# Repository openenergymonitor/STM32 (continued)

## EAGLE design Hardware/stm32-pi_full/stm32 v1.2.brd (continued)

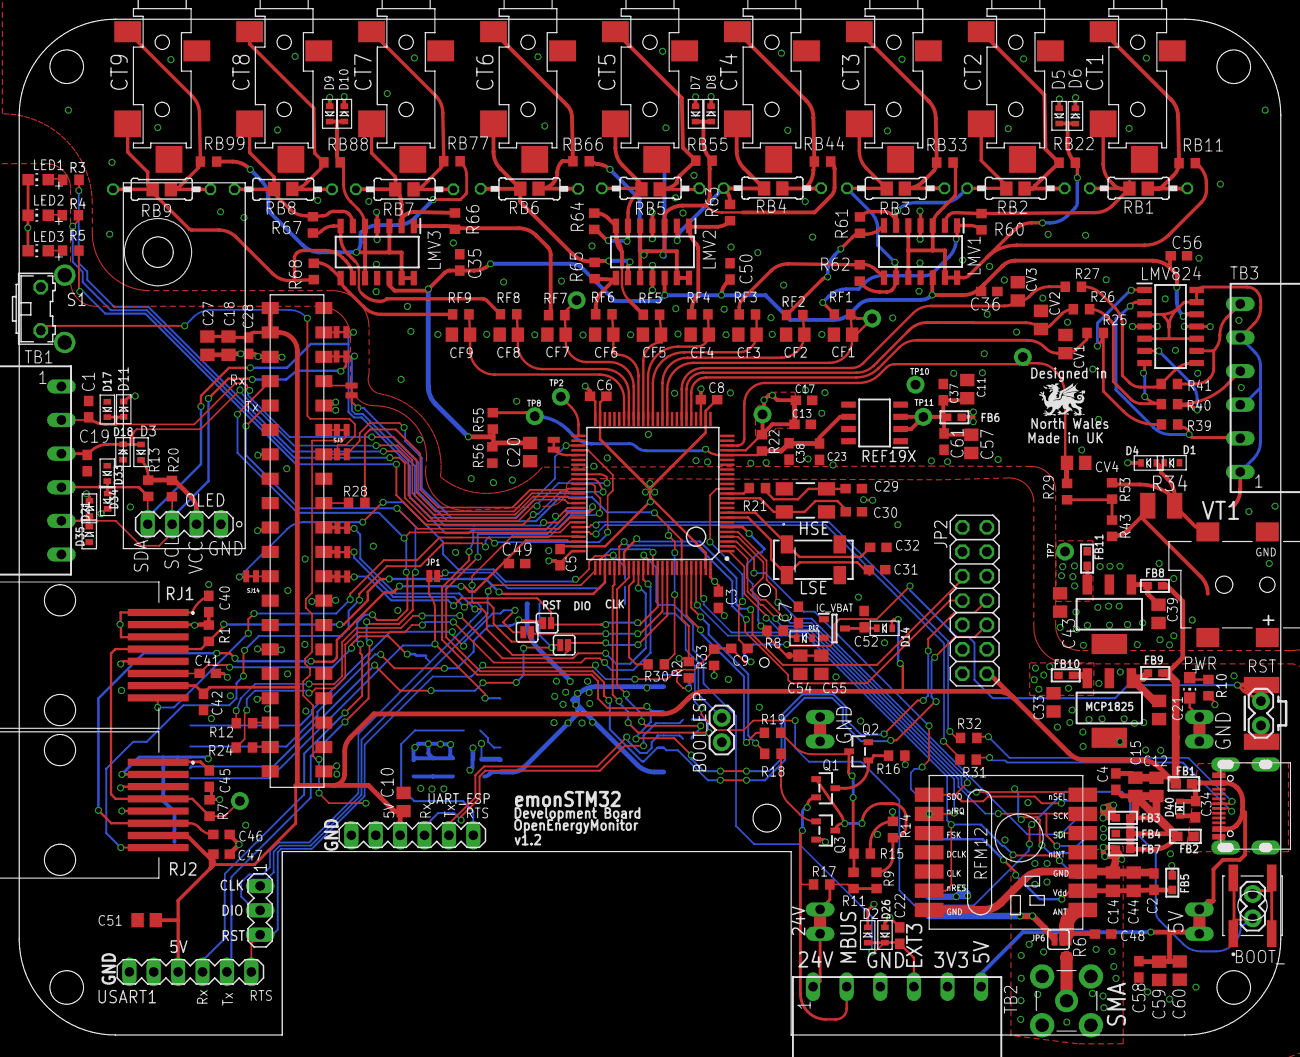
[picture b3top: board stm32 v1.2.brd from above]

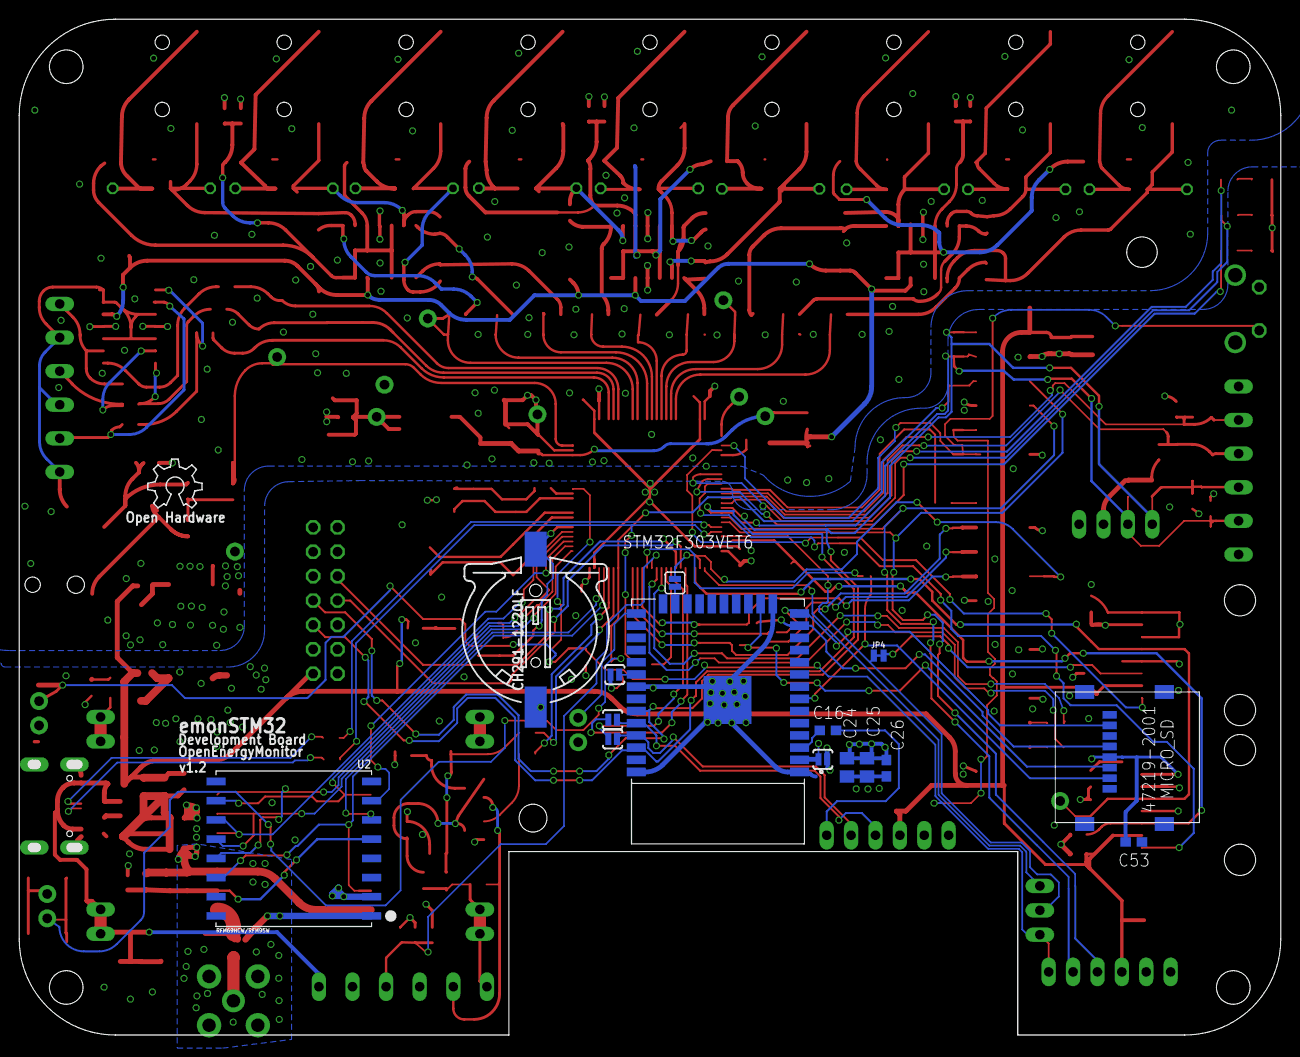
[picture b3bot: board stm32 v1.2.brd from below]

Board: 4 copper layers, 131.4 x 105.8 mm, 277 parts (16 on the bottom side), 164 nets.

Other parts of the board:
LOGO1: OSHW_LOGO_6MILX0200-NT; OSHW_6X200_NOTEXT

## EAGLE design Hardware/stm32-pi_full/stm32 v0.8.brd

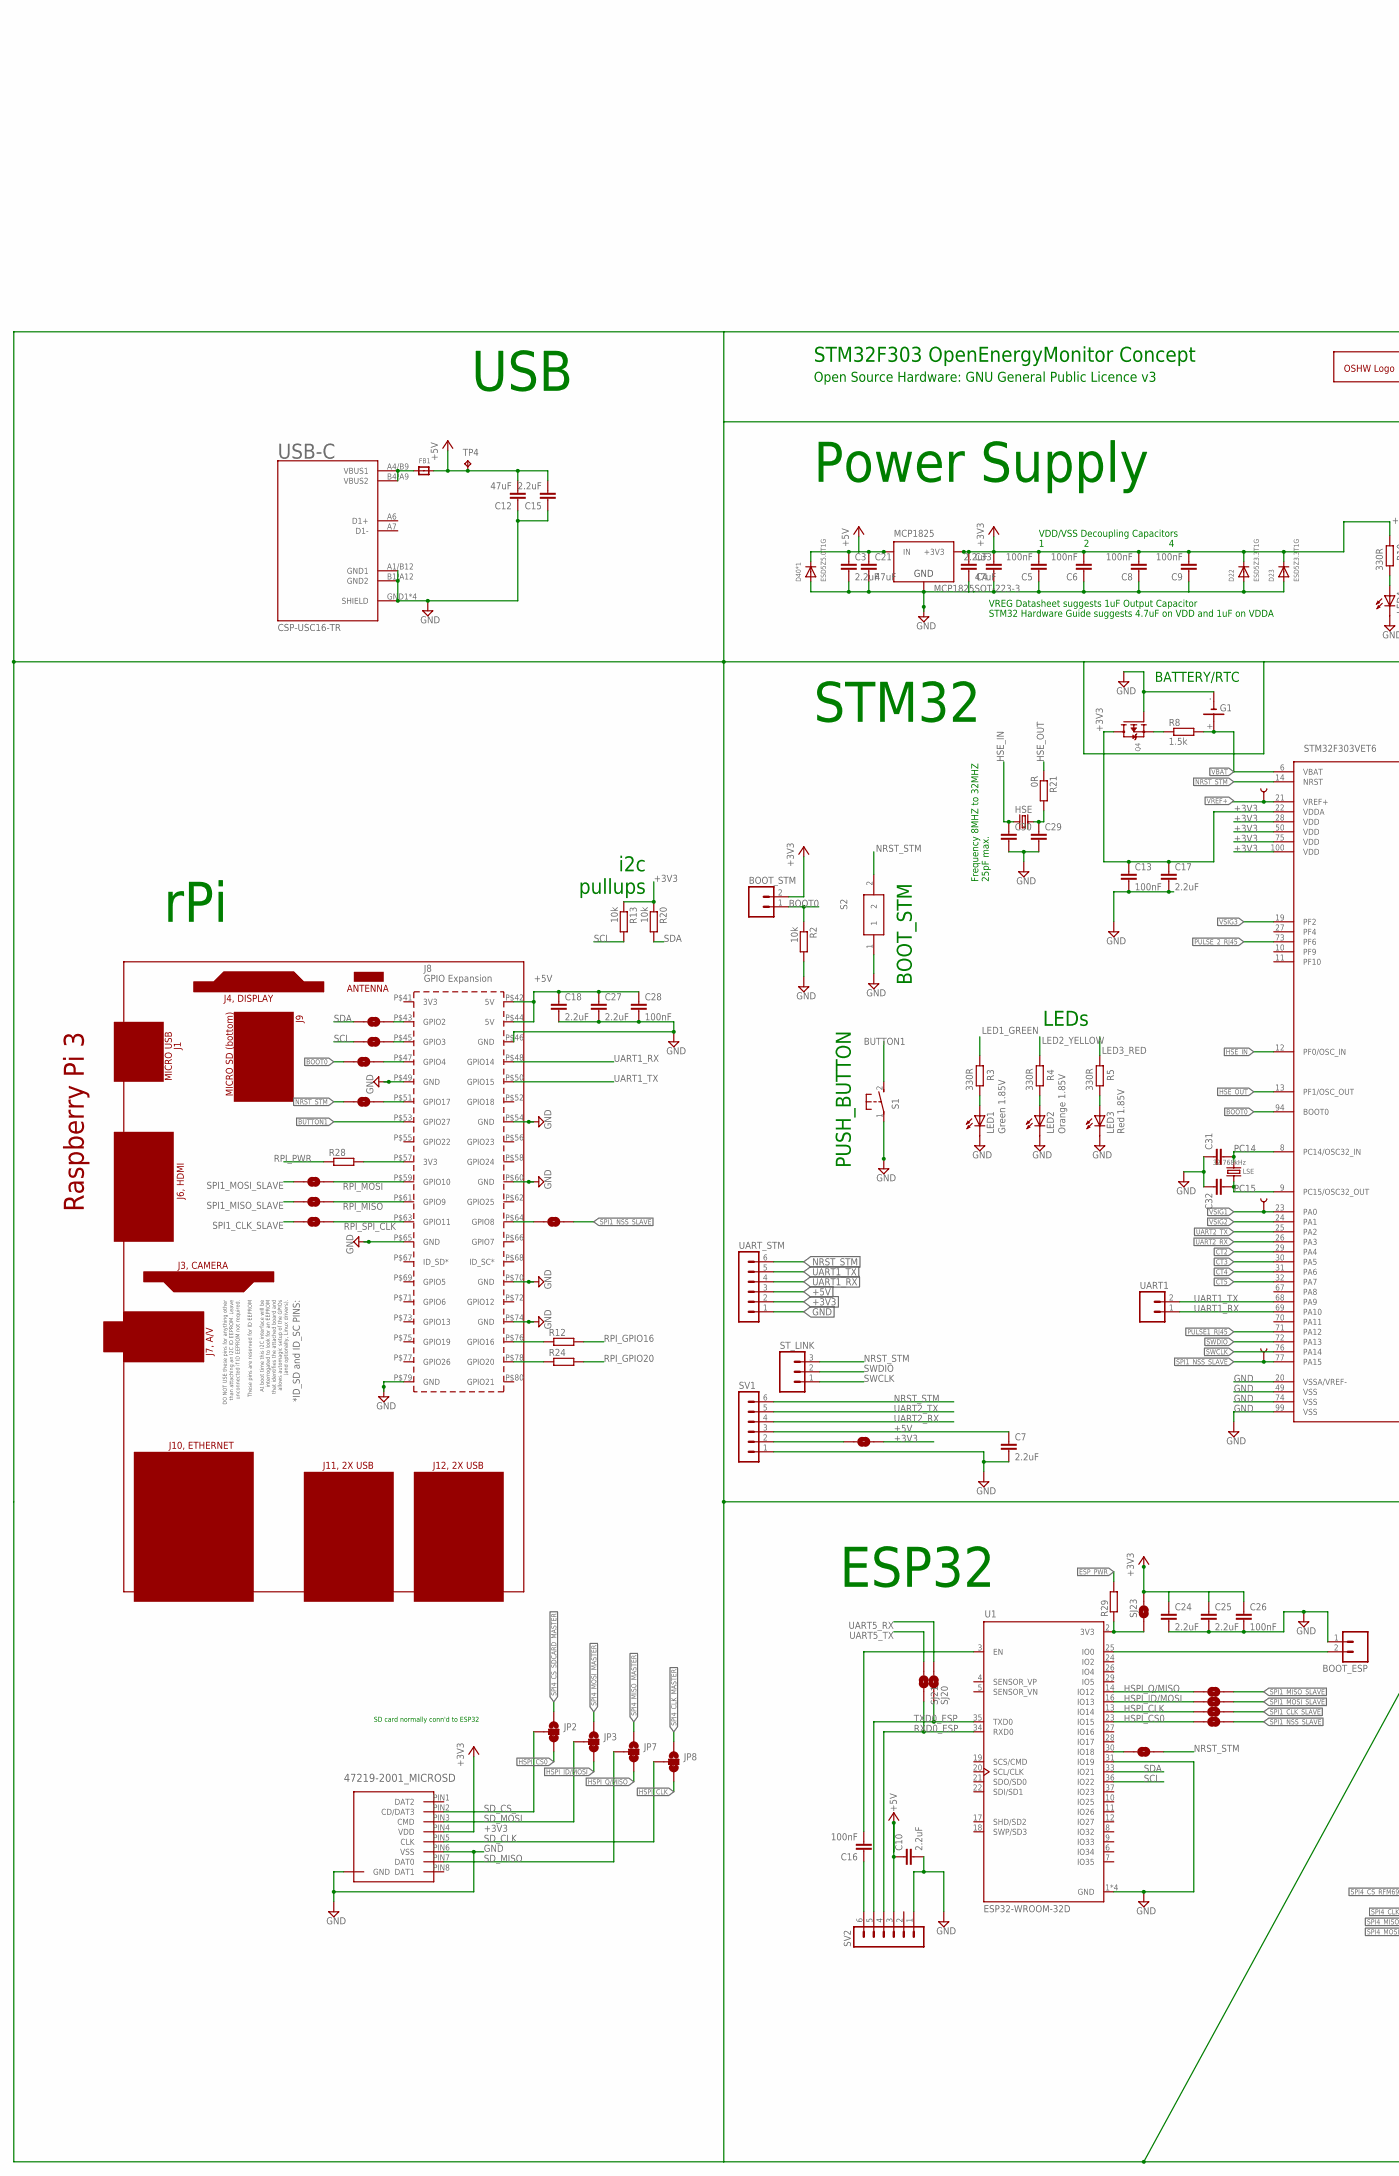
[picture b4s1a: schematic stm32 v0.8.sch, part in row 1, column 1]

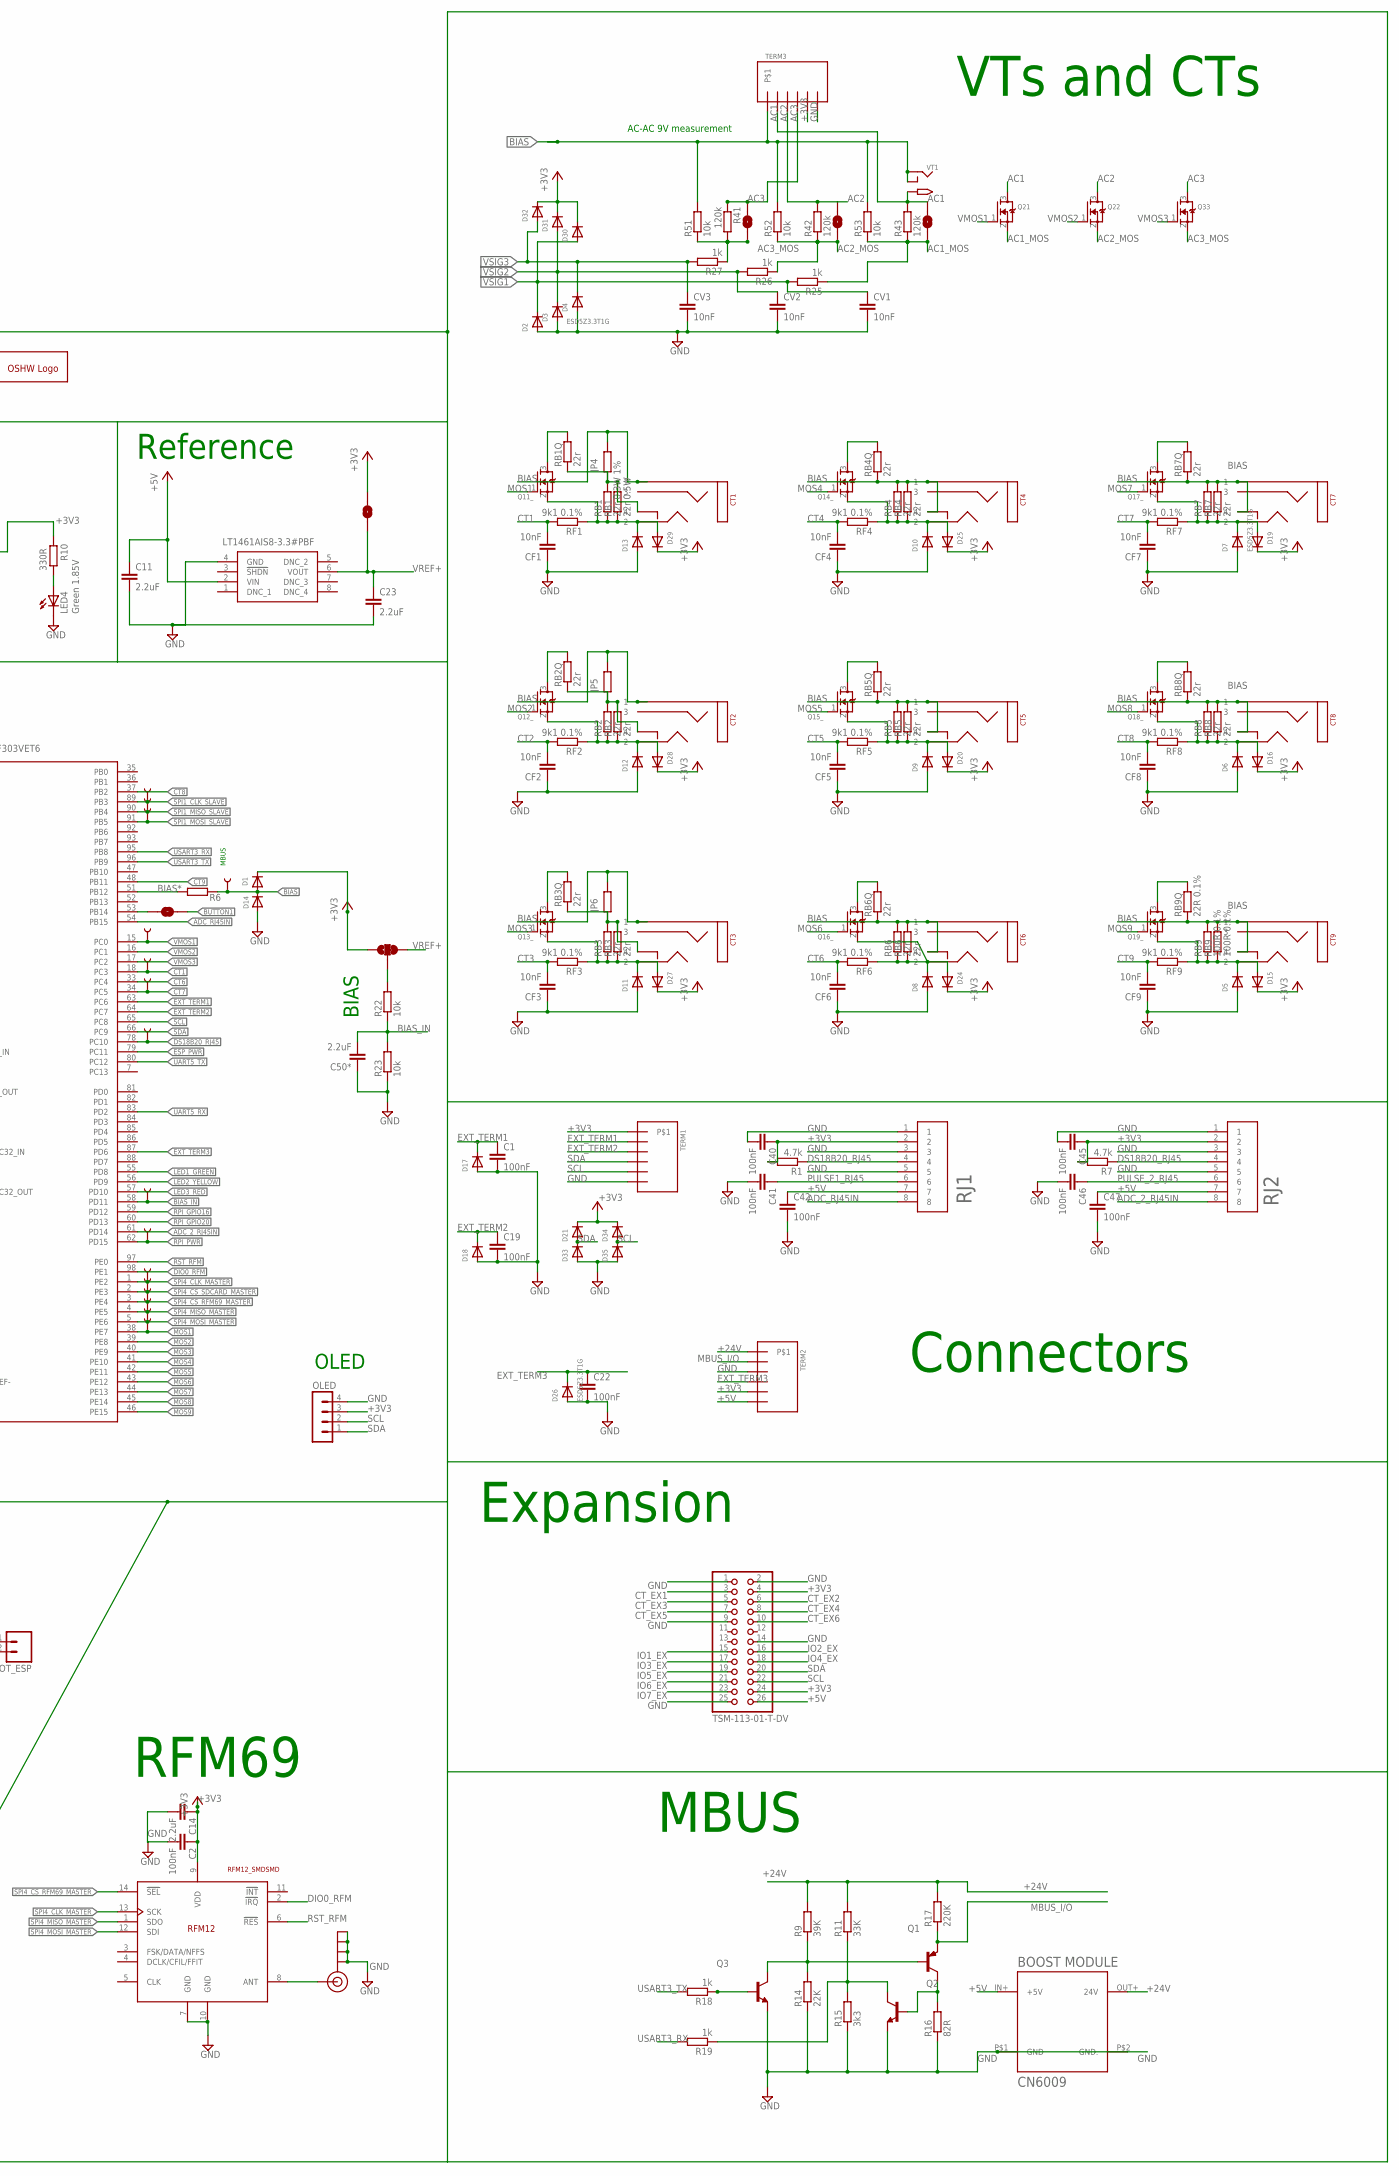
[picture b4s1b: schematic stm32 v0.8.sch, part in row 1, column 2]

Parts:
BOOT_ESP: M02PTH; 1X02
BOOT_STM: M02PTH; 1X02
C1, C2, C5, C6, C8, C9, C13, C16, C19, C22, C26, C28, C40, C41, C42, C45, C46, C47: 100nF; C0603
C3, C4, C7, C10, C11, C14, C15, C17, C18, C23, C24, C25, C27, C50*: 2.2uF; C0805
C12, C21, C33: 47uF; C0805
C29, C30: 15pF; C0603
C31, C32: 10pF; C0603
CF1, CF2, CF3, CF4, CF5, CF6, CF7, CF8, CF9: 10nF; C0603
CT1, CT2, CT3, CT4, CT5, CT6, CT7, CT8, CT9: SJ-3523-SMT; STEREO_SMT; MPN SJ-3523-SMT
CV1, CV2, CV3: 10nF; C0603
D1, D2, D3, D4, D5, D6, D7, D8, D9, D10, D11, D12, D13, D14, D15, D16, D17, D18, D19, D20, D21, D22, D23, D24, D25, D26, D27, D28, D29, D30, D31, D32, D33, D34, D35: ESD5Z3.3T1G; SOD-523
D40*1: ESD5Z5.0T1G; SOD-523
EXPANSION: TSM-113-01-T-DV; 2X13_SMT
FB1: FERRITE; 0603
G1: CH291-1220LF
GOLD_ORB_SM1: OSHWLOGOLOGO8MM; OSHW_8MM
HSE: 406C35E08M00000; CTS406
J1: SOLDERJUMPERNO; SJ_2S-NO
J$1: SMA_EDGE; SMA-EDGE
JP1: JUMPER-SMT_3_1-NC_TRACE_NO-SILK; SMT-JUMPER_3_1-NC_TRACE_NO-SILK
JP2, JP3, JP7, JP8: JUMPER-SMT_3_1-NC_TRACE_SILK; SMT-JUMPER_3_1-NC_TRACE_SILK
JP4, JP5, JP6: R-EU_R0603; R0603
LED1, LED4: Green 1.85V; CHIP-LED0805
LED2: Orange 1.85V; CHIP-LED0805
LED3: Red 1.85V; CHIP-LED0805
LSE: 32.768kHz; CRYSTAL_8X3.8
MCP1825: MCP1825SOT-223-3; SOT-223; MPN MCP1825S-3302E/DB
OLED: MA04-1-OLEDOLED; MA04-1-OLED
PCB2: RPI3YA; RPI3MIRROR2; MPN M20-7872042
PS1: LT1461AIS8-3.3#PBF; SOIC127P599X175-8N
Q1: MMBT3906; SOT23
Q2, Q3: MMBT3904; SOT23
Q4: MOSFET-P; SOT23-R
Q11_, Q12_, Q13_, Q14_, Q15_, Q16_, Q17_, Q18_, Q19_, Q21, Q22, Q33: MOSFET-NREFLOW; SOT23; MPN FDV303N
R1, R7: 4.7k; R0603
R2, R13, R20, R22, R23, R51, R52, R53: 10k; R0603
R3, R4, R5, R10: 330R; R0603
R6, R21: 0R; R0603
R8: 1.5k; R0603
R9: 39K; R0603
R11: 33K; R0603
R12, R24, R28, R29: 10K; R0603
R14: 22K; R0603
R15: 3k3; R0603
R16: 82R; R0603
R17: 220K; R0603
R18, R19, R25, R26, R27: 1k; R0603
R41, R42, R43: 120k; R0603
RB1: 22r 0.3W 1%; R1210
RB1Q, RB2, RB2Q, RB3, RB3Q, RB4, RB4Q, RB5, RB5Q, RB6, RB6Q, RB7, RB7Q, RB8, RB8Q: 22r; R1210
RB1_: 22r 0.5W; 0207/7
RB2_, RB3_, RB4_, RB5_, RB6_, RB7_, RB8_: 22r; 0207/7
RB9: 100R 0.1%; R1210
RB9Q: 22R 0.1%; R1210
RB9_: 100R 0.1%; 0207/7
RF1, RF2, RF3, RF4, RF5, RF6, RF7, RF8, RF9: 9k1 0.1%; R0603
RFM69HCW: RFM12_SMDSMD; RFM12
RJ1, RJ2: 95501-6889; 955016889
S1: 31-XX; B3F-31XX
S2: KSS221GLFS; KSS
SJ1, SJ2, SJ3, SJ5, SJ6, SJ7, SJ14, SJ20, SJ21, SJ23, SJ25, SJ26, SJ27, SJ32, SJ35, SJ36, SJ37: SOLDERJUMPERNO; SJ_2S-NO
SJ4, SJ9, SJ10, SJ13: JUMPER-SMT_2_NO_SILK; SMT-JUMPER_2_NO_SILK
STM32F303VET6: STM32F303VE; TQFP100; MPN STM32F303VET6
ST_LINK: 455-1750-1-ND; 1X03
SV1, SV2: MA06-1
TERM1, TERM2, TERM3: 3.5MM_TB_X6; 3.5MM_X6
TP1, TP2, TP3, TP11, TP12, TP13, TP14, TP15, TP16, TP21: TEST-POINT3; PAD.03X.03
TP4: TPB1,27; B1,27
TP5, TP6, TP7, TP9, TP10, TP17, TP18, TP19, TP20: TEST-POINTPOGO_PTH; 1X01_NO_SILK
U1: ESP32-WROOM-32D; MODULE_ESP32-WROOM-32D
U$2: BOOST_MODULE; BOOST
U$7: 47219-2001_MICROSD
UART1: M02PTH; 1X02
UART_STM: MA06-1
USB-C: CSP-USC16-TR; USB-C
VT1: ADC-028-2-T; DCJACK_2MM_SMT; MPN ADC-028-1-T

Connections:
+3V3: BOOT_STM.2, C2.1, C4.2, C5.2, C6.2, C8.2, C9.2, C13.1, C14.1, C17.1, C24.1, C25.1, C26.1, C33.1, C40.1, C45.1, D1.K (C), D15.K (C), D16.K (C), D19.K (C), D20.K (C), D21.K (C), D22.K (C), D23.K (C), D24.K (C), D25.K (C), D27.K (C), D28.K (C), D29.K (C), D30.K (C), D31.K (C), D32.K (C), D34.K (C), EXPANSION.4, EXPANSION.24, JP1.1, MCP1825.3 (+3V3), OLED.3, Q4.3 (D), R1.2, R7.2, R10.2, R13.1, R20.1, RFM69HCW.9 (VDD), RJ1.2, RJ2.2, SJ1.2, SJ2.2, SJ23.2, STM32F303VET6.22 (VDDA), STM32F303VET6.28 (VDD), STM32F303VET6.50 (VDD), STM32F303VET6.75 (VDD), STM32F303VET6.100 (VDD), TERM1.P$1, TERM2.P$5, TERM3.P$5, U$7.PIN4 (VDD), UART_STM.2
+5V: C3.1, C7.1, C10.1, C11.1, C12.2, C15.2, C18.1, C21.1, C27.1, C28.1, C42.1, C47.1, D40*1.K (C), EXPANSION.26, FB1.2, MCP1825.1 (IN), PCB2.P$42 (5V), PCB2.P$44 (5V), PS1.2 (VIN), RJ1.7, RJ2.7, SV1.3, SV2.3, TERM2.P$6, TP4.TP, U$2.IN+ (+5V), UART_STM.3
+24V: R9.2, R11.2, R17.2, TERM2.P$1, U$2.OUT+ (24V)
AC1: Q21.3 (D), R43.2, SJ37.2, TERM3.P$2, VT1.PWR2 (TIP)
AC1_MOS: Q21.2 (S), R25.1, R43.1, R53.1, SJ37.1
AC2: Q22.3 (D), R42.2, SJ36.2, TERM3.P$3
AC2_MOS: Q22.2 (S), R26.1, R42.1, R52.1, SJ36.1
AC3: Q33.3 (D), R41.1, SJ35.2, TERM3.P$4
AC3_MOS: Q33.2 (S), R27.1, R41.2, R51.1, SJ35.1
ADC_2_RJ45IN: RJ2.8, STM32F303VET6.61 (PD14)
ADC_RJ45IN: RJ1.8, STM32F303VET6.54 (PB15)
ANT: J$1.SIG (SIGNAL), RFM69HCW.8 (ANT)
BIAS: CT1.P$1 (1), CT2.P$1 (1), CT3.P$1 (1), CT4.P$1 (1), CT4.P$4 (4), CT5.P$1 (1), CT5.P$4 (4), CT6.P$1 (1), CT6.P$4 (4), CT7.P$1 (1), CT7.P$4 (4), CT8.P$1 (1), CT8.P$4 (4), CT9.P$1 (1), CT9.P$4 (4), D1.A, D14.K (C), JP4.2, JP5.2, JP6.2, R6.1, R51.2, R52.2, R53.2, RB4.2, RB4Q.1, RB4_.2, RB5.2, RB5Q.1, RB5_.2, RB6.2, RB6Q.1, RB6_.2, RB7.2, RB7Q.1, RB7_.2, RB8.2, RB8Q.1, RB8_.2, RB9.2, RB9Q.1, RB9_.2, TERM3.P$1, TP5.1, VT1.GND (RING), VT1.GNDBREAK (RING_SW)
BIAS*: R6.2, STM32F303VET6.51 (PB12)
BIAS_IN: C50*.2, R22.1, R23.2, STM32F303VET6.58 (PD11), TP10.1
BOOT0: BOOT_STM.1, J1.1, R2.1, STM32F303VET6.94 (BOOT0)
BOOT0_RPI: J1.2, PCB2.P$47 (GPIO4)
BUTTON1: PCB2.P$53 (GPIO27), S1.2 (S), SJ3.1
BUTTON1_STM: SJ3.2, STM32F303VET6.53 (PB14)
CT1: CF1.2, RF1.2, STM32F303VET6.18 (PC3), TP18.1
CT2: CF2.2, RF2.2, STM32F303VET6.29 (PA4)
CT3: CF3.2, RF3.2, STM32F303VET6.30 (PA5)
CT4: CF4.2, RF4.2, STM32F303VET6.31 (PA6)
CT5: CF5.2, RF5.2, STM32F303VET6.32 (PA7)
CT6: CF6.2, RF6.2, STM32F303VET6.33 (PC4)
CT7: CF7.2, RF7.2, STM32F303VET6.34 (PC5), TP19.1
CT8: CF8.2, RF8.2, STM32F303VET6.37 (PB2)
CT9: CF9.2, RF9.2, STM32F303VET6.48 (PB11)
CT_EX1: EXPANSION.3
CT_EX2: EXPANSION.6
CT_EX3: EXPANSION.5
CT_EX4: EXPANSION.8
CT_EX5: EXPANSION.7
CT_EX6: EXPANSION.10
CT_IN1: CT1.P$2 (2), D13.K (C), D29.A, Q11_.2 (S), RB1.1, RB1_.1, RF1.1
CT_IN2: CT2.P$2 (2), D12.K (C), D28.A, Q12_.2 (S), RB2.1, RB2_.1, RF2.1
CT_IN3: CT3.P$2 (2), D11.K (C), D27.A, Q13_.2 (S), RB3.1, RB3_.1, RF3.1
DIO0_RFM: RFM69HCW.2 (!IRQ), STM32F303VET6.98 (PE1)
DS18B20_RJ45: R1.1, R7.1, RJ1.4, RJ2.4, STM32F303VET6.78 (PC10), TP9.1
ESP_PWR: R29.2, STM32F303VET6.79 (PC11)
ESP_PWR_PRE: R29.1, SJ23.1, U1.2 (3V3)
EXT_TERM1: C1.1, D17.K (C), STM32F303VET6.63 (PC6), TERM1.P$2
EXT_TERM2: C19.1, D18.K (C), STM32F303VET6.64 (PC7), TERM1.P$3
EXT_TERM3: C22.1, D26.K (C), STM32F303VET6.87 (PD6), TERM2.P$4
GND: BOOT_ESP.1, C1.2, C2.2, C3.2, C4.1, C5.1, C6.1, C7.2, C8.1, C9.1, C10.2, C11.2, C12.1, C13.2, C14.2, C15.1, C17.2, C18.2, C19.2, C21.2, C22.2, C23.2, C24.2, C25.2, C26.2, C27.2, C28.2, C29.2, C30.2, C31.2, C32.2, C33.2, C40.2, C41.2, C42.2, C45.2, C46.2, C47.2, C50*.1, CF1.1, CF2.1, CF3.1, CF4.1, CF5.1, CF6.1, CF7.1, CF8.1, CF9.1, CV1.2, CV2.2, CV3.2, D2.A, D3.A, D4.A, D5.A, D6.A, D7.A, D8.A, D9.A, D10.A, D11.A, D12.A, D13.A, D14.A, D17.A, D18.A, D22.A, D23.A, D26.A, D33.A, D35.A, D40*1.A, EXPANSION.1, EXPANSION.2, EXPANSION.9, EXPANSION.14, EXPANSION.25, G1.-, J$1.GND@0 (GND), J$1.GND@1 (GND), J$1.GND@2 (GND), J$1.GND@3 (GND), LED1.C, LED2.C, LED3.C, LED4.C, MCP1825.2 (GND), MCP1825.4 (GND), OLED.4, PCB2.P$46 (GND), PCB2.P$49 (GND), PCB2.P$54 (GND), PCB2.P$60 (GND), PCB2.P$65 (GND), PCB2.P$70 (GND), PCB2.P$74 (GND), PCB2.P$79 (GND), PS1.4 (GND), Q2.2 (E), Q3.2 (E), Q4.1 (G), R2.2, R14.1, R15.1, R16.1, R23.1, RFM69HCW.7 (GND), RFM69HCW.10 (GND), RJ1.1, RJ1.3, RJ1.5, RJ2.1, RJ2.3, RJ2.5, S1.1, S2.1, STM32F303VET6.20 (VSSA/VREF-), STM32F303VET6.49 (VSS), STM32F303VET6.74 (VSS), STM32F303VET6.99 (VSS), SV1.1, SV2.1, TERM1.P$6, TERM2.P$3, TERM3.P$6, U1.1 (GND), U1.15 (GND), U1.31 (IO19), U1.38 (GND), U1.39 (GND), U$2.P$1 (GND), U$2.P$2 (GND.), U$7.P$1 (GND), U$7.P$2 (GND), U$7.P$3 (GND), U$7.P$4 (GND), U$7.PIN6 (VSS), UART_STM.1, USB-C.A1/B12 (GND1), USB-C.B1/A12 (GND2), USB-C.GND1 (SHIELD), USB-C.GND2 (SHIELD), USB-C.GND3 (SHIELD), USB-C.GND4 (SHIELD)
HSE_IN: C30.1, HSE.1, STM32F303VET6.12 (PF0/OSC_IN)
HSE_OUT: R21.1, STM32F303VET6.13 (PF1/OSC_OUT)
HSE_OUT_: C29.1, HSE.3 (2), R21.2
HSPI_CLK: JP8.3, SJ10.1, U1.13 (IO14)
HSPI_CS0: JP2.3, SJ13.1, U1.23 (IO15)
HSPI_ID/MOSI: JP3.3, SJ9.1, U1.16 (IO13)
HSPI_Q/MISO: JP7.3, SJ4.1, U1.14 (IO12)
IO1_EX: EXPANSION.15
IO2_EX: EXPANSION.16
IO3_EX: EXPANSION.17
IO4_EX: EXPANSION.18
IO5_EX: EXPANSION.19
IO6_EX: EXPANSION.21
IO7_EX: EXPANSION.23
LED1_GREEN: R3.2, STM32F303VET6.55 (PD8)
LED2_YELLOW: R4.2, STM32F303VET6.56 (PD9)
LED3_RED: R5.2, STM32F303VET6.57 (PD10)
MBUS_I/O: Q1.2 (E), R17.1, TERM2.P$2
MOS1: Q11_.1 (G), STM32F303VET6.38 (PE7), TP17.1
MOS2: Q12_.1 (G), STM32F303VET6.39 (PE8)
MOS3: Q13_.1 (G), STM32F303VET6.40 (PE9)
MOS4: Q14_.1 (G), STM32F303VET6.41 (PE10)
MOS5: Q15_.1 (G), STM32F303VET6.42 (PE11)
MOS6: Q16_.1 (G), STM32F303VET6.43 (PE12)
MOS7: Q17_.1 (G), STM32F303VET6.44 (PE13)
MOS8: Q18_.1 (G), STM32F303VET6.45 (PE14)
MOS9: Q19_.1 (G), STM32F303VET6.46 (PE15)
unnamed: SJ1.1, SV1.2
unnamed: CT9.P$2 (2), D5.K (C), D15.A, Q19_.2 (S), RB9.1, RB9_.1, RF9.1
unnamed: LED2.A, R4.1
unnamed: LED3.A, R5.1
unnamed: FB1.1, USB-C.A4/B9 (VBUS1), USB-C.B4/A9 (VBUS2)
unnamed: CT8.P$2 (2), D6.K (C), D16.A, Q18_.2 (S), RB8.1, RB8_.1, RF8.1
unnamed: LED4.A, R10.1
unnamed: CT7.P$2 (2), D7.K (C), D19.A, Q17_.2 (S), RB7.1, RB7_.1, RF7.1
unnamed: PCB2.P$64 (GPIO8), SJ14.1
unnamed: JP1.2, R22.2
unnamed: C16.1, SV2.6
unnamed: C16.2, U1.3 (EN)
unnamed: Q4.2 (S), R8.1
unnamed: BOOT_ESP.2, U1.25 (IO0)
unnamed: PCB2.P$57 (3V3), R28.2
unnamed: Q11_.3 (D), RB1Q.2
unnamed: Q12_.3 (D), RB2Q.2
unnamed: Q13_.3 (D), RB3Q.2
unnamed: CT1.P$4 (4), JP4.1, RB1.2, RB1Q.1, RB1_.2
unnamed: CT2.P$4 (4), JP5.1, RB2.2, RB2Q.1, RB2_.2
unnamed: CT3.P$4 (4), JP6.1, RB3.2, RB3Q.1, RB3_.2
unnamed: Q1.3 (C), Q2.1 (B), R16.2
unnamed: Q1.1 (B), Q3.3 (C), R9.1, R14.2
unnamed: Q2.3 (C), R11.1, R15.2, R19.1
unnamed: Q3.1 (B), R18.1
unnamed: Q14_.3 (D), RB4Q.2
unnamed: CT6.P$2 (2), D8.K (C), D24.A, Q16_.2 (S), RB6.1, RB6_.1, RF6.1
unnamed: CT5.P$2 (2), D9.K (C), D20.A, Q15_.2 (S), RB5.1, RB5_.1, RF5.1
unnamed: CT4.P$2 (2), D10.K (C), D25.A, Q14_.2 (S), RB4.1, RB4_.1, RF4.1
unnamed: LED1.A, R3.1
unnamed: Q19_.3 (D), RB9Q.2
unnamed: Q18_.3 (D), RB8Q.2
unnamed: Q15_.3 (D), RB5Q.2
unnamed: Q16_.3 (D), RB6Q.2
unnamed: Q17_.3 (D), RB7Q.2
NRST_STM: S2.2, SJ25.2, SJ32.1, STM32F303VET6.14 (NRST), ST_LINK.3, SV1.6, UART_STM.6
NRST_STM_ESP: SJ25.1, U1.30 (IO18)
NRST_STM_RPI: PCB2.P$51 (GPIO17), SJ32.2
PC14: C31.1, LSE.P$1 (1), STM32F303VET6.8 (PC14/OSC32_IN)
PC15: C32.1, LSE.P$4 (2), STM32F303VET6.9 (PC15/OSC32_OUT)
PULSE1_RJ45: C41.1, RJ1.6, STM32F303VET6.71 (PA12)
PULSE_2_RJ45: C46.1, RJ2.6, STM32F303VET6.73 (PF6)
RPI_GPIO16: R12.2, STM32F303VET6.59 (PD12)
RPI_GPIO16_RPI: PCB2.P$76 (GPIO16), R12.1
RPI_GPIO20: R24.2, STM32F303VET6.60 (PD13)
RPI_GPIO20_RPI: PCB2.P$78 (GPIO20), R24.1
RPI_MISO: PCB2.P$61 (GPIO9), SJ6.2
RPI_MOSI: PCB2.P$59 (GPIO10), SJ5.2
RPI_PWR: R28.1, STM32F303VET6.62 (PD15), TP11.P$1
RPI_SPI_CLK: PCB2.P$63 (GPIO11), SJ7.2
RST_RFM: RFM69HCW.6 (!RES), STM32F303VET6.97 (PE0)
RXD0_ESP: SJ21.2, SV2.4, U1.34 (RXD0)
SCL: D34.A, D35.K (C), EXPANSION.22, OLED.2, R13.2, SJ27.2, STM32F303VET6.65 (PC8), TERM1.P$5, U1.36 (IO22)
SCL_: PCB2.P$45 (GPIO3), SJ27.1
SDA: D21.A, D33.K (C), EXPANSION.20, OLED.1, R20.2, SJ26.1, STM32F303VET6.66 (PC9), TERM1.P$4, U1.33 (IO21)
SDA_: PCB2.P$43 (GPIO2), SJ26.2
SD_CLK: JP8.2, U$7.PIN5 (CLK)
SD_CS_: JP2.2, U$7.PIN2 (CD/DAT3)
SD_MISO: JP7.2, U$7.PIN7 (DAT0)
SD_MOSI: JP3.2, U$7.PIN3 (CMD)
SPI1_CLK_SLAVE: SJ7.1, SJ10.2, STM32F303VET6.89 (PB3), TP1.P$1
SPI1_MISO_SLAVE: SJ4.2, SJ6.1, STM32F303VET6.90 (PB4), TP2.P$1
SPI1_MOSI_SLAVE: SJ5.1, SJ9.2, STM32F303VET6.91 (PB5), TP3.P$1
SPI1_NSS_SLAVE: SJ13.2, SJ14.2, STM32F303VET6.77 (PA15), TP21.P$1
SPI4_CLK_MASTER: JP8.1, RFM69HCW.13 (SCK), STM32F303VET6.1 (PE2), TP12.P$1
SPI4_CS_RFM69_MASTER: RFM69HCW.14 (!SEL), STM32F303VET6.3 (PE4), TP14.P$1
SPI4_CS_SDCARD_MASTER: JP2.1, STM32F303VET6.2 (PE3), TP13.P$1
SPI4_MISO_MASTER: JP7.1, RFM69HCW.1 (SDO), STM32F303VET6.4 (PE5), TP15.P$1
SPI4_MOSI_MASTER: JP3.1, RFM69HCW.12 (SDI), STM32F303VET6.5 (PE6), TP16.P$1
SWCLK: STM32F303VET6.76 (PA14), ST_LINK.1
SWDIO: STM32F303VET6.72 (PA13), ST_LINK.2
TXD0_ESP: SJ20.2, SV2.5, U1.35 (TXD0)
UART1_RX: PCB2.P$48 (GPIO14), STM32F303VET6.69 (PA10), UART1.1, UART_STM.4
UART1_TX: PCB2.P$50 (GPIO15), STM32F303VET6.68 (PA9), UART1.2, UART_STM.5
UART2_RX: STM32F303VET6.26 (PA3), SV1.4
UART2_TX: STM32F303VET6.25 (PA2), SV1.5
UART5_RX: SJ20.1, STM32F303VET6.83 (PD2)
UART5_TX: SJ21.1, STM32F303VET6.80 (PC12)
USART3_RX: R19.2, STM32F303VET6.95 (PB8)
USART3_TX: R18.2, STM32F303VET6.96 (PB9)
VBAT: G1.+, R8.2, STM32F303VET6.6 (VBAT)
VMOS1: Q21.1 (G), STM32F303VET6.15 (PC0), TP6.1
VMOS2: Q22.1 (G), STM32F303VET6.16 (PC1)
VMOS3: Q33.1 (G), STM32F303VET6.17 (PC2)
VREF+: C23.1, JP1.3, PS1.6 (VOUT), SJ2.1, STM32F303VET6.21 (VREF+), TP7.1
VSIG1: CV1.1, D2.K (C), D30.A, R25.2, STM32F303VET6.23 (PA0), TP20.1
VSIG2: CV2.1, D3.K (C), D31.A, R26.2, STM32F303VET6.24 (PA1)
VSIG3: CV3.1, D4.K (C), D32.A, R27.2, STM32F303VET6.19 (PF2)

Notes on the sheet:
VDD/VSS Decoupling Capacitors
VREG Datasheet suggests 1uF Output Capacitor
STM32 Hardware Guide suggests 4.7uF on VDD and 1uF on VDDA
AC-AC 9V measurement
VTs and CTs
STM32F303 OpenEnergyMonitor Concept
Power Supply
STM32
Open Source Hardware: GNU General Public Licence v3
Frequency 8MHZ to 32MHZ 25pF max.
Reference
ESP32
MBUS
rPi
BOOT_STM
RFM69
Connectors
Expansion
LEDs
PUSH_BUTTON
OLED
BIAS
USB
BATTERY/RTC
i2c pullups
SD card normally conn'd to ESP32
